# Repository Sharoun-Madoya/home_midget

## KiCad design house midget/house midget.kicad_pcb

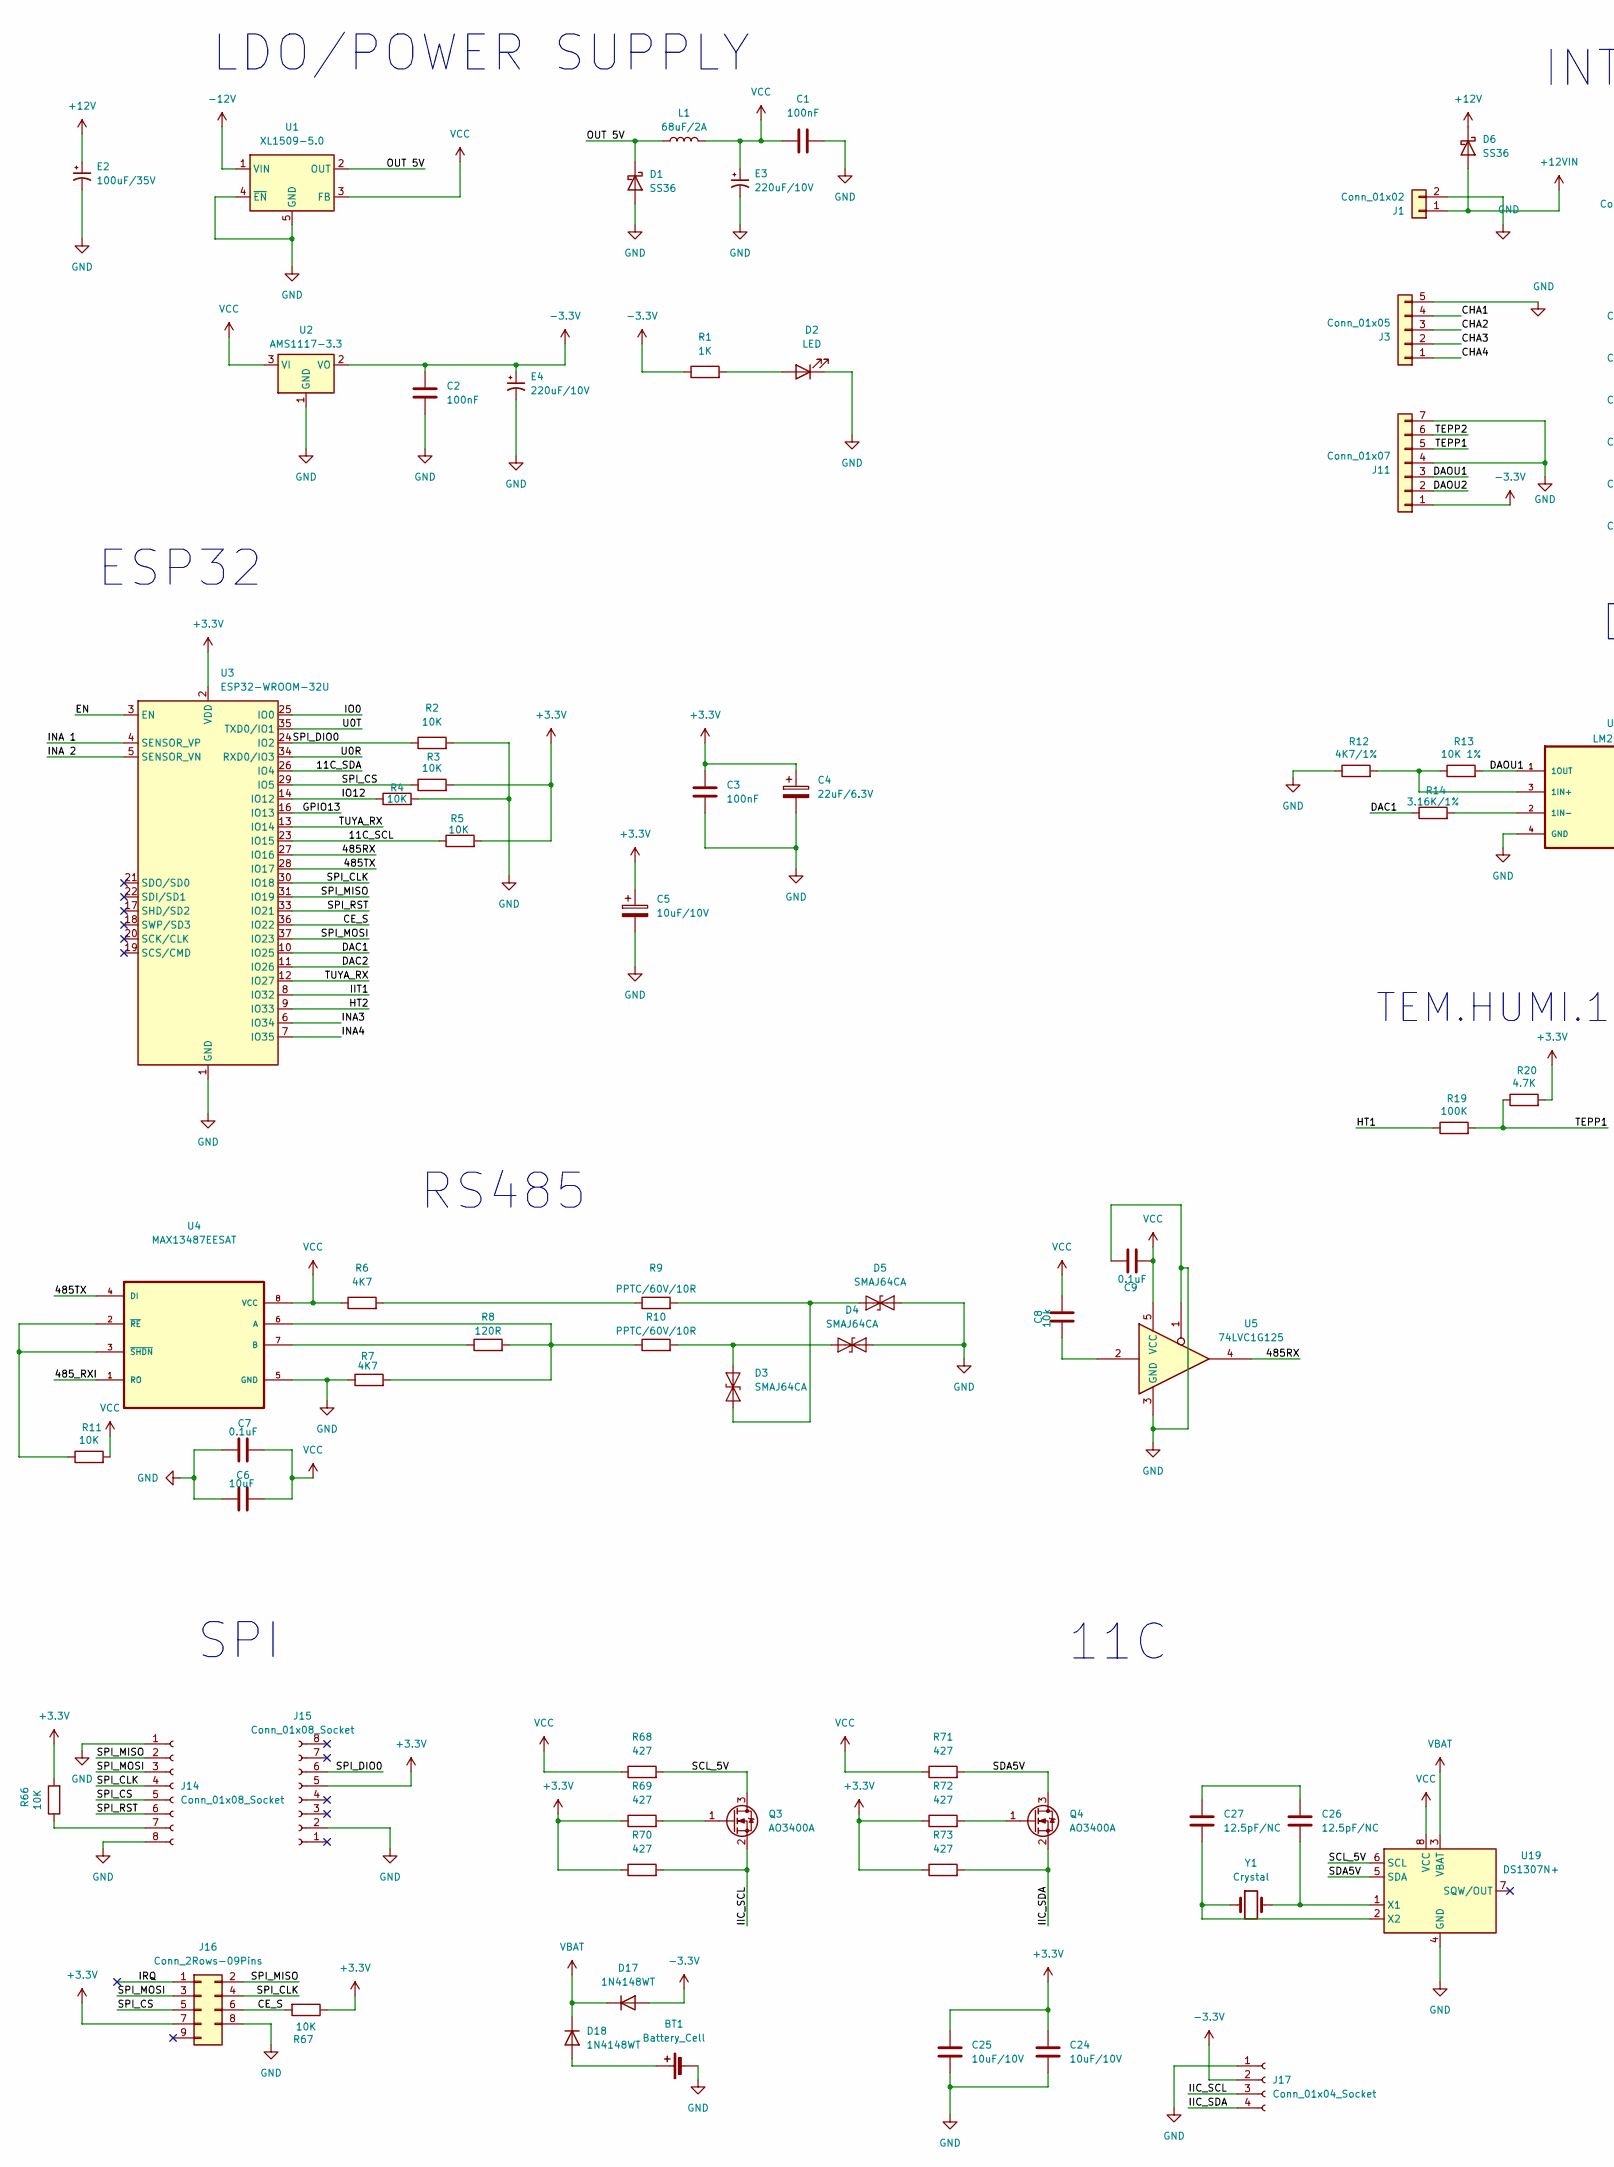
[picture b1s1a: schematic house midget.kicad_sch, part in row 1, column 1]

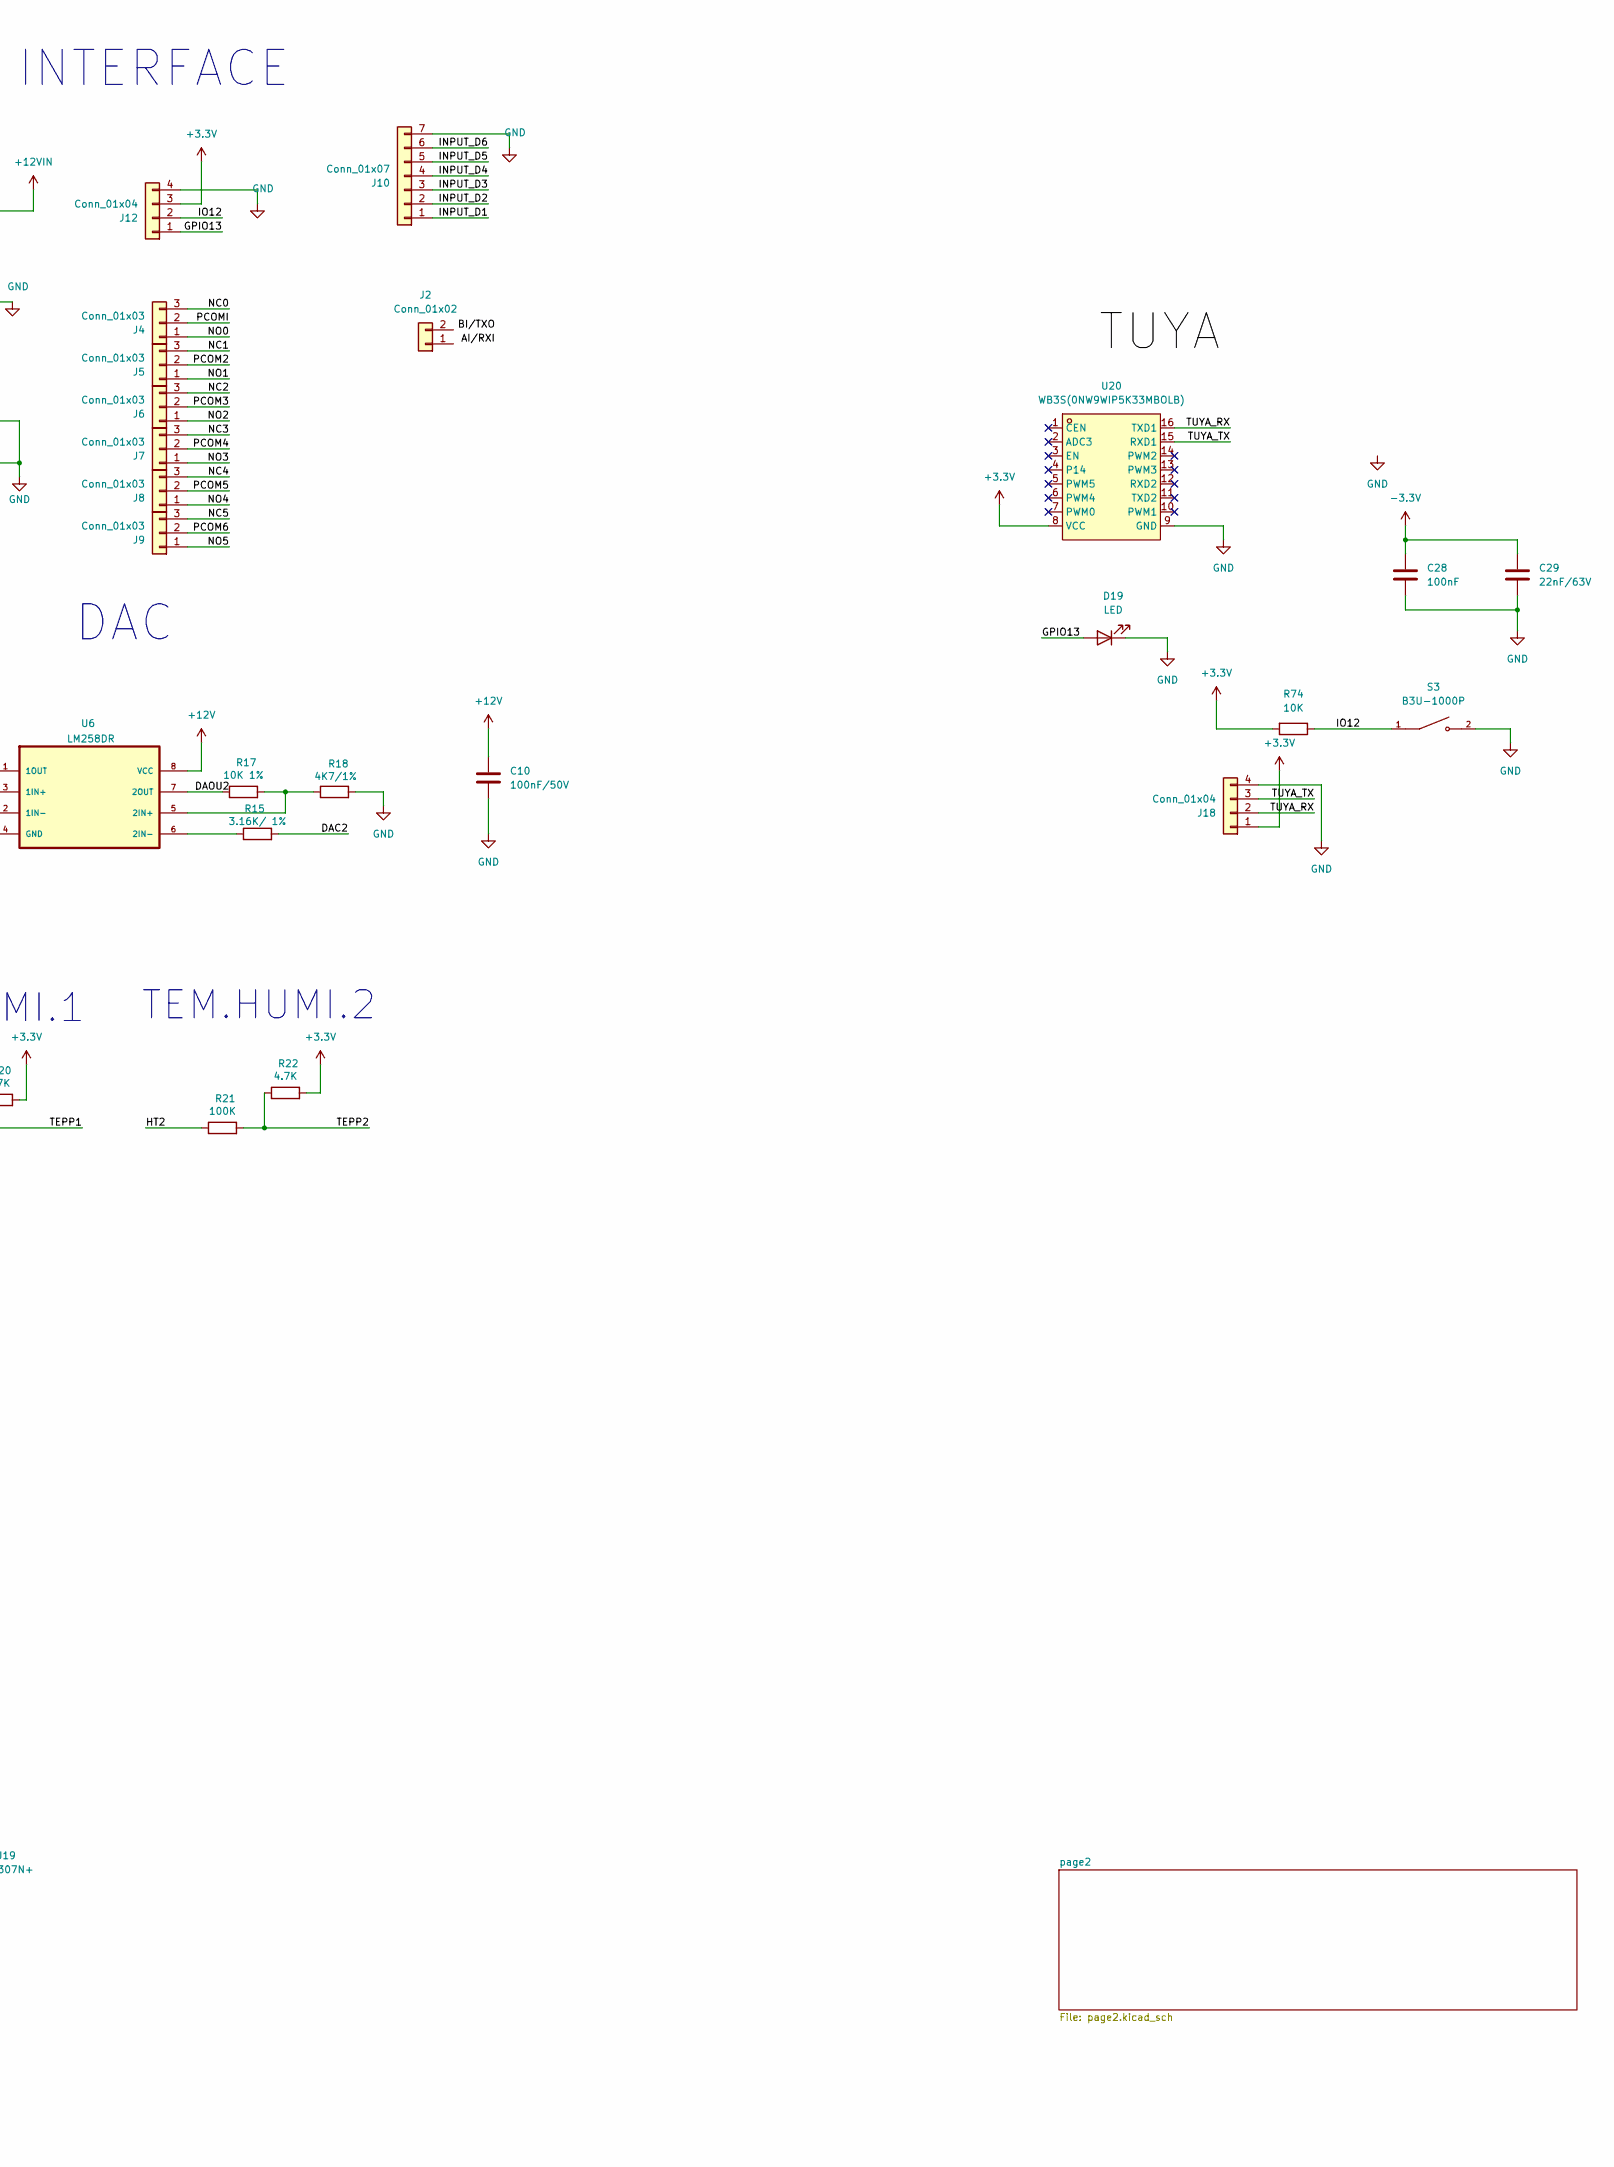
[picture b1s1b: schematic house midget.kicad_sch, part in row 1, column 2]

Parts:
BT1: Battery_Cell; BatteryHolder_MPD_BH-18650-PC2
C1, C2, C3, C28: 100nF; CP_EIA-3216-18_Kemet-A
C4: 22uF/6.3V; CP_EIA-3528-21_Kemet-B
C5, C24, C25: 10uF/10V; CP_EIA-2012-12_Kemet-R
C6: 10uF; CP_EIA-2012-12_Kemet-R
C7, C9: 0.1uF; C_1825_4564Metric
C8: 10k; CP_EIA-2012-12_Kemet-R
C10: 100nF/50V; CP_EIA-3216-18_Kemet-A
C26, C27: 12.5pF/NC; CP_EIA-2012-12_Kemet-R
C29: 22nF/63V; CP_EIA-3528-21_Kemet-B
D1: SS36; D_DO-35_SOD27_P7.62mm_Horizontal
D2, D19: LED; LED_Cree-XP
D3, D4, D5: SMAJ64CA; D_SMA
D6: SS36; D_SMA
D17, D18: 1N4148WT; D_SOD-523
E2: 100uF/35V; C_1808_4520Metric_Pad1.72x2.30mm_HandSolder
E3, E4: 220uF/10V; C_1808_4520Metric_Pad1.72x2.30mm_HandSolder
J1, J2: Conn_01x02; Flipper_Zero_Angled
J3: Conn_01x05; Flipper_Zero_Angled
J4, J5, J6, J7, J8, J9: Conn_01x03; Flipper_Zero_Angled
J10, J11: Conn_01x07; Flipper_Zero_Angled
J12, J18: Conn_01x04; Flipper_Zero_Angled
J14, J15: Conn_01x08_Socket; Flipper_Zero_Angled
J16: Conn_2Rows-09Pins; Flipper_Zero_Straight
J17: Conn_01x04_Socket; Flipper_Zero_Angled
L1: 68uF/2A; L_Sunlord_MWSA0605S
Q3, Q4: AO3400A; SOT-23
R1: 1K; R_1206_3216Metric
R2, R3, R4, R5, R11, R74: 10K; R_0805_2012Metric
R6, R7: 4K7; R_Axial_DIN0309_L9.0mm_D3.2mm_P15.24mm_Horizontal
R8: 120R; R_Axial_DIN0309_L9.0mm_D3.2mm_P15.24mm_Horizontal
R9, R10: PPTC/60V/10R; R_Axial_DIN0309_L9.0mm_D3.2mm_P15.24mm_Horizontal
R12, R18: 4K7/1%; R_Axial_DIN0309_L9.0mm_D3.2mm_P15.24mm_Horizontal
R13, R17: 10K 1%; R_0805_2012Metric
R14: 3.16K/1%; R_1206_3216Metric
R15: 3.16K/ 1%; R_1206_3216Metric
R19, R21: 100K; R_Axial_DIN0309_L9.0mm_D3.2mm_P15.24mm_Horizontal
R20, R22: 4.7K; R_Axial_DIN0309_L9.0mm_D3.2mm_P15.24mm_Horizontal
R66, R67: 10K; R_0201_0603Metric
R68, R69, R70, R71, R72, R73: 427; R_01005_0402Metric_Pad0.57x0.30mm_HandSolder
S3: B3U-1000P; SW_B3U-1000P; DigiKey_Part_Number SW1020TR-ND
U1: XL1509-5.0; SOIC-8_3.9x4.9mm_P1.27mm
U2: AMS1117-3.3; SOT-223-3_TabPin2
U3: ESP32-WROOM-32U
U4: MAX13487EESAT; SOIC127P600X175-8N
U5: 74LVC1G125; SOIC127P600X175-14N
U6: LM258DR; SOIC127P599X175-8N; DigiKey_Part_Number 296-14591-2-ND
U19: DS1307N+; DIP-8_W7.62mm
U20: WB3S(0NW9WIP5K33MBOLB); WB3S-SMD_OEAKA9ADCKYHKZYS; LCSC Part C2830108
Y1: Crystal; Oscillator_SMD_Fox_FT5H_5.0x3.2mm

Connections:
+3.3V: C3.2, C4.1, C5.1, C24.1, C25.1, J12.3, J15.5, J16.7, J18.1, R3.2, R5.2, R20.2, R22.2, R66.2, R67.1, R69.1, R70.1, R72.1, R73.1, R74.2, U3.2 (VDD), U20.8 (VCC); also elsewhere on the board
+12V: C10.2, D6.1 (K), E2.1, U6.8 (VCC)
+12VIN: D6.2 (A), J1.1; also elsewhere on the board
-3.3V: C2.2, C28.1, C29.1, D17.2 (A), E4.1, J11.1, J17.2, R1.1, U2.2 (VO); also elsewhere on the board
-12V: U1.1 (VIN)
/11C_SCL: R5.1, U3.23 (IO15)
/11C_SDA: U3.26 (IO4)
/485RX: U3.27 (IO16), U5.4
/485TX: U3.28 (IO17), U4.4 (DI)
/CE_S: J16.6, R67.2, U3.36 (IO22)
/CHA1: J3.4
/CHA2: J3.3
/CHA3: J3.2
/CHA4: J3.1
/DAC1: R14.1, U3.10 (IO25)
/DAC2: R15.2, U3.11 (IO26)
/DAOU1: J11.3, R13.2, U6.1 (1OUT)
/DAOU2: J11.2, R17.1, U6.7 (2OUT)
/EN: U3.3 (EN)
/GPIO13: D19.2 (A), J12.1, U3.16 (IO13)
/HT1: R19.1
/HT2: R21.1, U3.9 (IO33)
/IIC_SCL: J17.3, Q3.2 (S), R70.2
/IIC_SDA: J17.4, Q4.2 (S), R73.2
/IIT1: U3.8 (IO32)
/INA3: U3.6 (IO34)
/INA4: U3.7 (IO35)
/INA 1: U3.4 (SENSOR_VP)
/INA 2: U3.5 (SENSOR_VN)
/INPUT_D1: J10.1
/INPUT_D2: J10.2
/INPUT_D3: J10.3
/INPUT_D4: J10.4
/INPUT_D5: J10.5
/INPUT_D6: J10.6
/IO0: U3.25 (IO0)
/IO12: J12.2, R4.1, R74.1, S3.1, U3.14 (IO12)
/IRQ: J16.1
/NC0: J4.3
/NC1: J5.3
/NC2: J6.3
/NC3: J7.3
/NC4: J8.3
/NC5: J9.3
/NO0: J4.1
/NO1: J5.1
/NO2: J6.1
/NO3: J7.1
/NO4: J8.1
/NO5: J9.1
/OUT 5V: D1.1 (K), L1.1, U1.2 (OUT)
/PCOM2: J5.2
/PCOM3: J6.2
/PCOM4: J7.2
/PCOM5: J8.2
/PCOM6: J9.2
/PCOMI: J4.2
/SCL_5V: Q3.3 (D), R68.2, U19.6 (SCL)
/SDA5V: Q4.3 (D), R71.2, U19.5 (SDA)
/SPI_CLK: J14.4, J16.4, U3.30 (IO18)
/SPI_CS: J14.5, J16.5, R3.1, U3.29 (IO5)
/SPI_DIO0: J15.6, R2.1, U3.24 (IO2)
/SPI_MISO: J14.2, J16.2, U3.31 (IO19)
/SPI_MOSI: J14.3, J16.3, U3.37 (IO23)
/SPI_RST: J14.6, U3.33 (IO21)
/TEPP1: J11.5, R19.2, R20.1
/TEPP2: J11.6, R21.2, R22.1
/TUYA_RX: J18.2, U3.12 (IO27), U3.13 (IO14), U20.16 (TXD1)
/TUYA_TX: J18.3, U20.15 (RXD1)
/U0R: U3.34 (RXD0/IO3)
/U0T: U3.35 (TXD0/IO1)
GND: BT1.2 (-), C1.2, C2.1, C3.1, C4.2, C5.2, C6.2, C7.2, C9.1, C10.1, C24.2, C25.2, C28.2, C29.2, D1.2 (A), D2.1 (K), D4.1 (A1), D5.1 (A1), D19.1 (K), E2.2, E3.2, E4.2, J1.2, J3.5, J10.7, J11.4, J11.7, J12.4, J14.1, J14.8, J15.2, J16.8, J17.1, J18.4, R2.2, R4.2, R7.1, R12.1, R18.2, S3.2, U1.4 (~EN), U1.5 (GND), U1.6 (GND), U1.7 (GND), U1.8 (GND), U2.1 (GND), U3.1 (GND), U3.15 (GND), U3.38 (GND), U3.39 (GND), U4.5 (GND), U5.1, U5.3 (GND), U6.4 (GND), U19.4 (GND), U20.9 (GND); also elsewhere on the board
unnamed: BT1.1 (+), D18.2 (A)
unnamed: C8.2, U5.2
unnamed: C26.1, C27.1
unnamed: D2.2 (A), R1.2
unnamed: D3.1 (A1), D5.2 (A2), R9.2
unnamed: D3.2 (A2), D4.2 (A2), R10.2
unnamed: J14.7, R66.1
unnamed: Q3.1 (G), R69.2
unnamed: Q4.1 (G), R72.2
unnamed: R6.2, R9.1
unnamed: R7.2, R8.2, R10.1, U4.6 (A)
unnamed: R8.1, U4.7 (B)
unnamed: R11.1, U4.2 (~RE), U4.3 (~SHDN)
unnamed: R12.2, R13.1, U6.3 (1IN+)
unnamed: R14.2, U6.2 (1IN-)
unnamed: R17.2, R18.1, U6.5 (2IN+)
unnamed: R15.1, U6.6 (2IN-)
unnamed: C26.2, U19.1 (X1), Y1.2
unnamed: C27.2, U19.2 (X2), Y1.1
VBAT: D17.1 (K), D18.1 (K), U19.3 (VBAT)
VCC: C1.1, C6.1, C7.1, C8.1, C9.2, E3.1, L1.2, R6.1, R11.2, R68.1, R71.1, U1.3 (FB), U2.3 (VI), U4.8 (VCC), U5.5 (VCC), U19.8 (VCC); also elsewhere on the board

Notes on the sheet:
ESP32
11C
DAC
RS485
TEM.HUMI.2
INTERFACE
TEM.HUMI.1
SPI
LDO/POWER SUPPLY

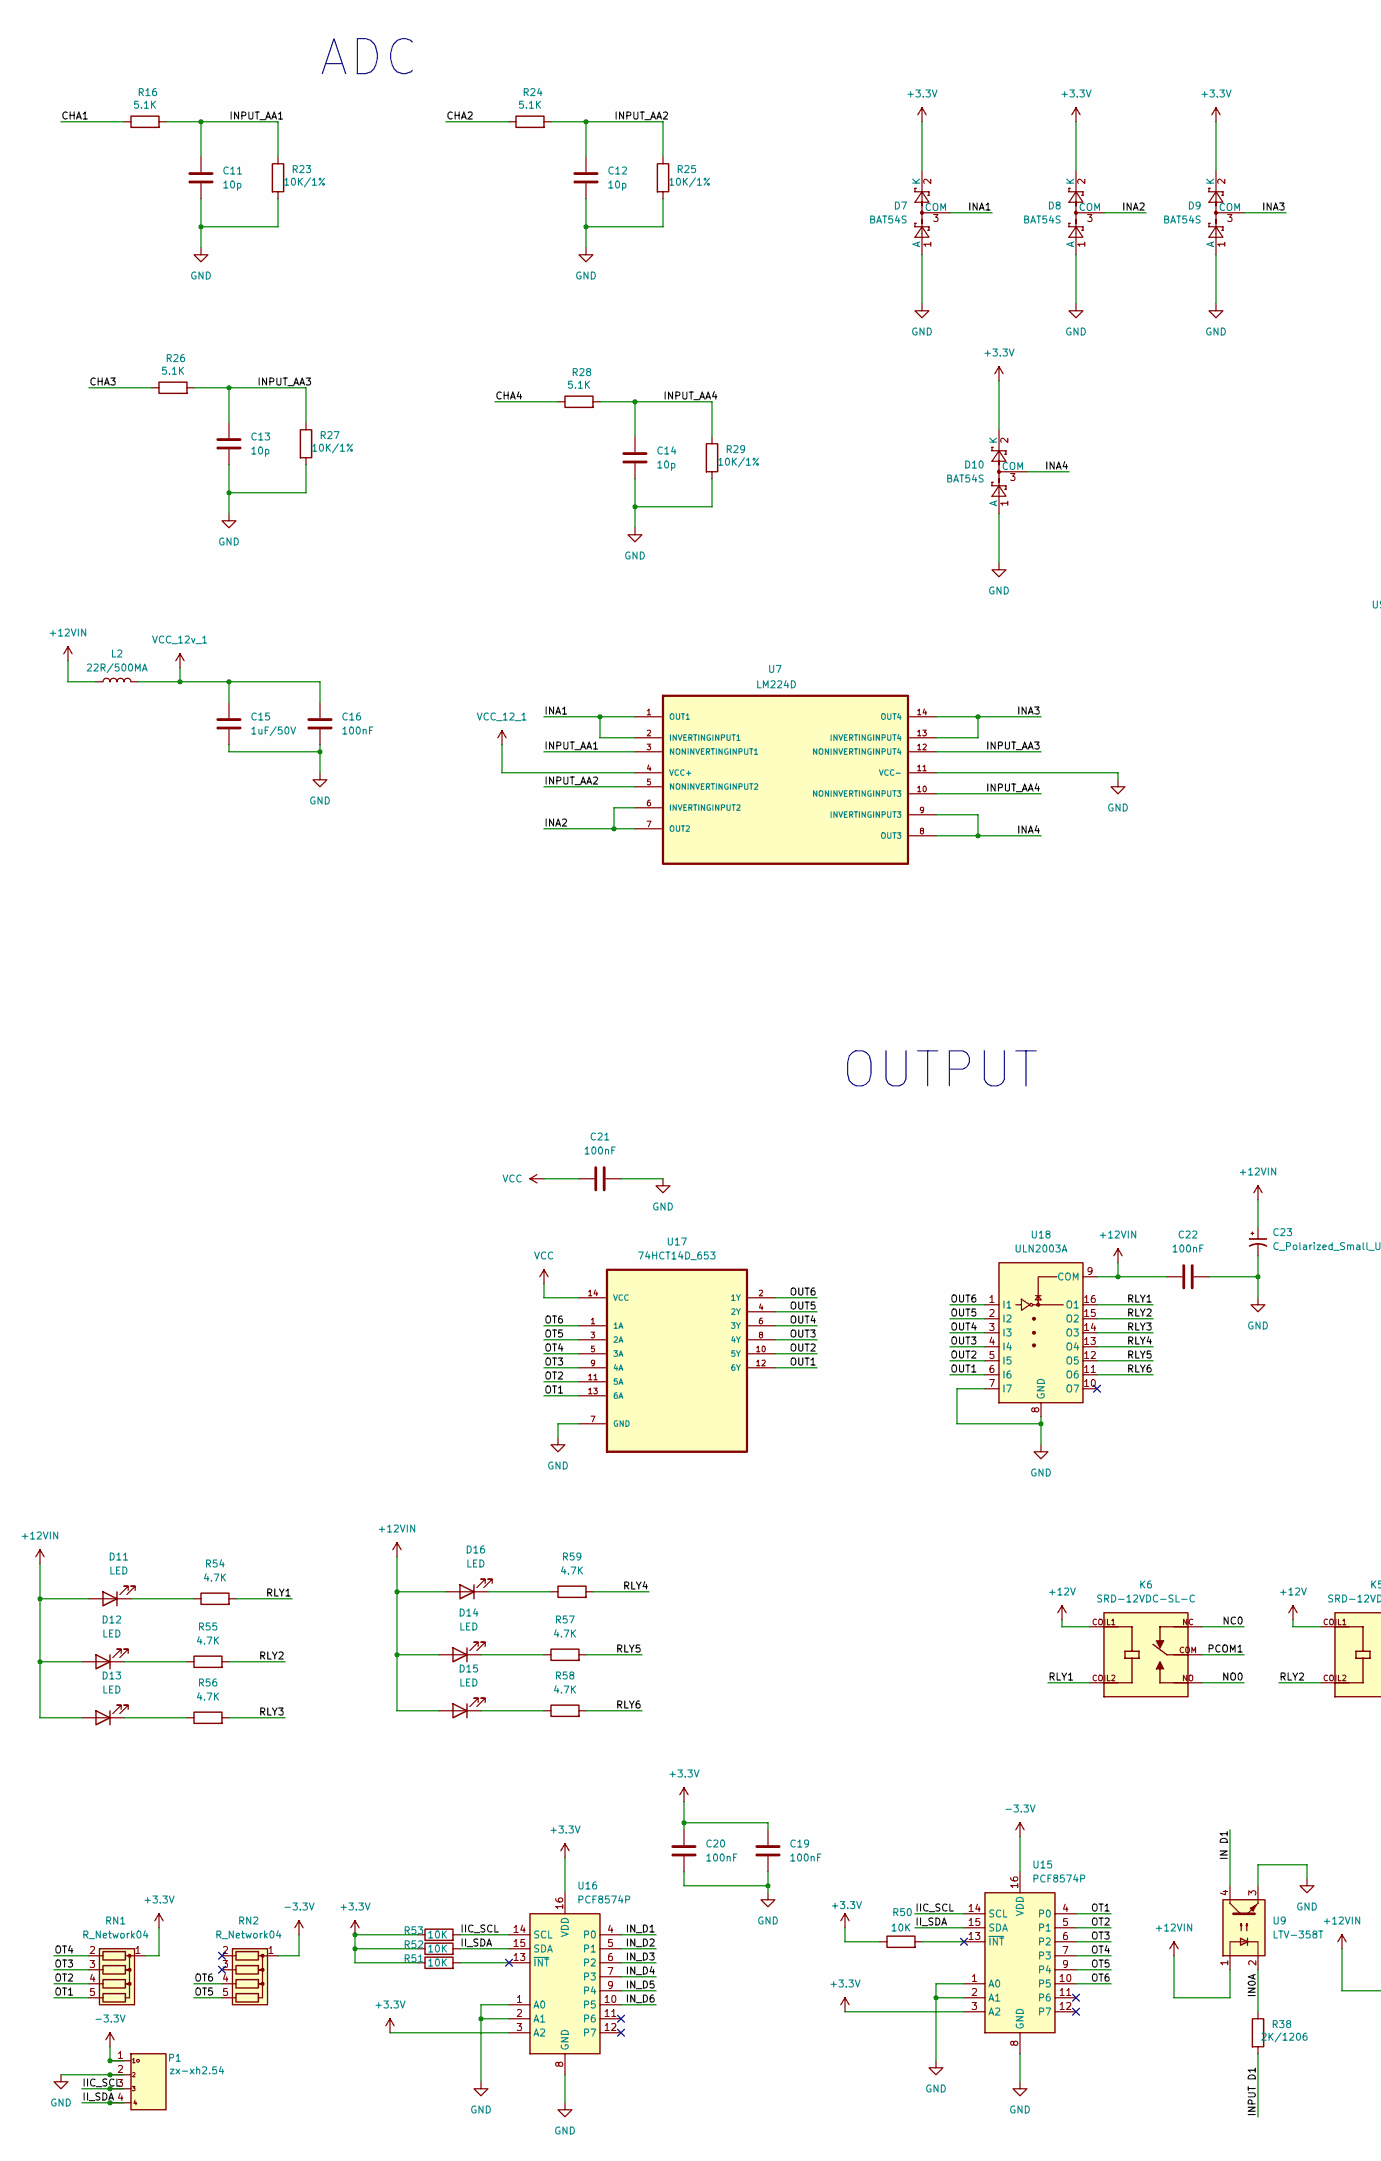
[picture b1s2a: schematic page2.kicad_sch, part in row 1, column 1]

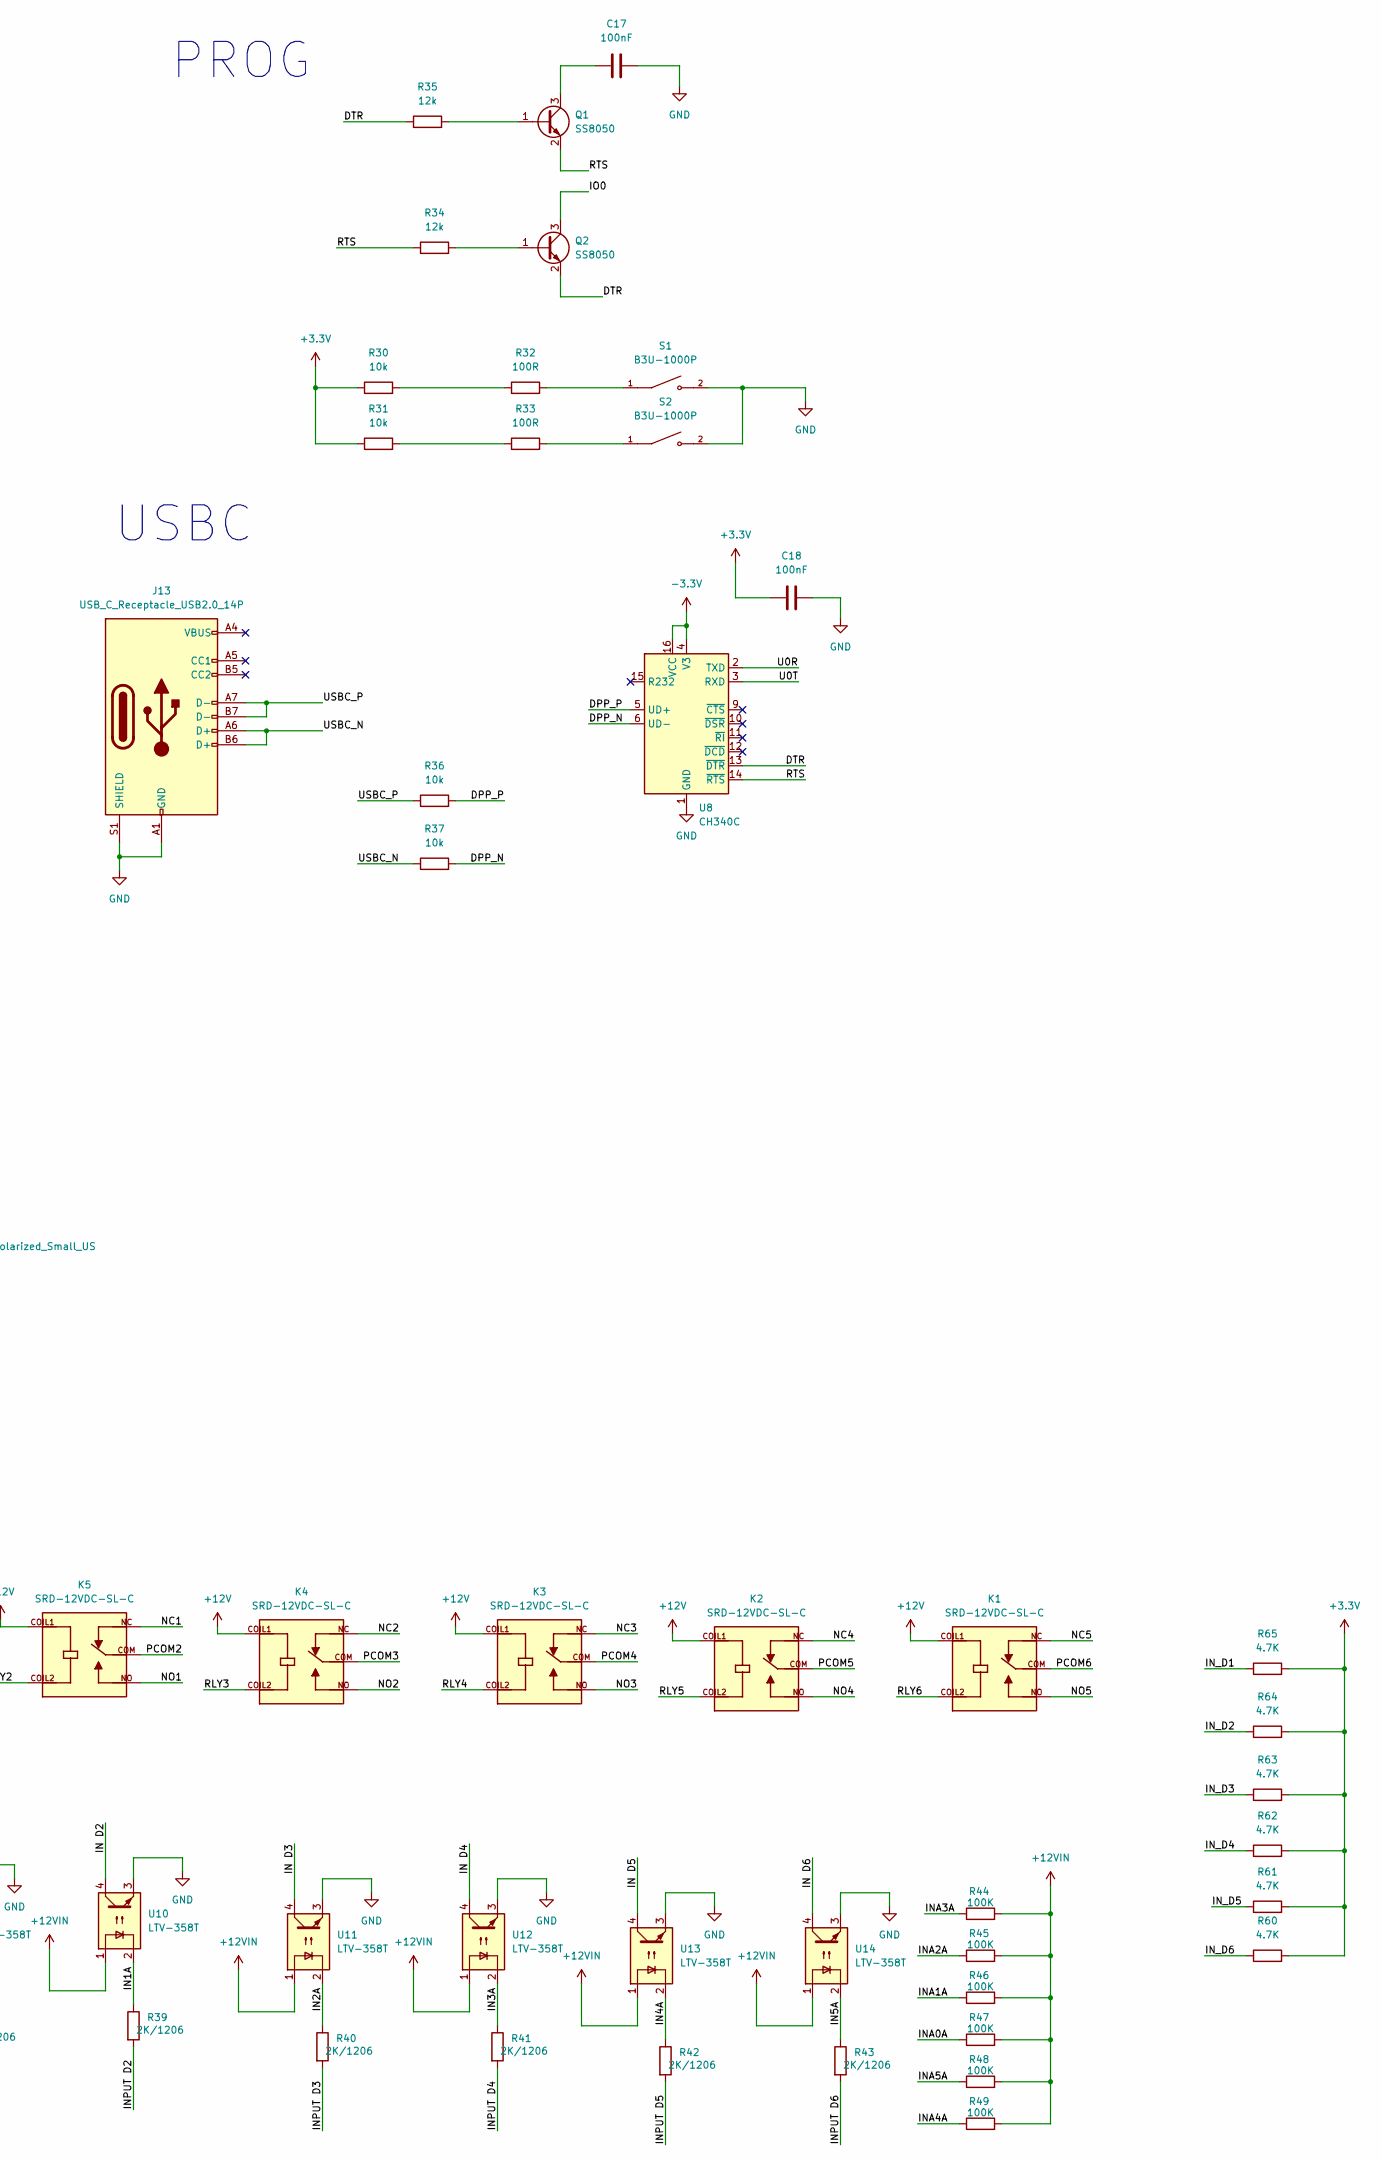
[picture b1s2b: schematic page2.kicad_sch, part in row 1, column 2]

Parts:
C11, C12, C13, C14: 10p; CP_EIA-2012-12_Kemet-R
C15: 1uF/50V; C_1825_4564Metric
C16, C17, C18, C19, C20, C21, C22: 100nF; CP_EIA-3216-18_Kemet-A
C23: C_Polarized_Small_US; C_1825_4564Metric
D7, D8, D9, D10: BAT54S; SOT-23
D11, D12, D13, D14, D15, D16: LED; LED_Cree-XP
J13: USB_C_Receptacle_USB2.0_14P; USB_C_Receptacle_GCT_USB4105-xx-A_16P_TopMnt_Horizontal
K1, K2, K3, K4, K5, K6: SRD-12VDC-SL-C; RELAY_SRD-12VDC-SL-C; PARTREV 1.0
L2: 22R/500MA; L_Sunlord_MWSA0605S
P1: zx-xh2.54; L_Sunlord_MWSA0605S
Q1, Q2: SS8050; SOT-23
R16, R24, R26, R28: 5.1K; R_Axial_DIN0309_L9.0mm_D3.2mm_P15.24mm_Horizontal
R23, R25, R27, R29: 10K/1%; R_0805_2012Metric
R30, R31, R36, R37: 10k; R_0805_2012Metric
R32, R33: 100R; R_1218_3246Metric
R34, R35: 12k; R_0805_2012Metric
R38, R39, R40, R41, R42, R43: 2K/1206; R_1206_3216Metric
R44, R45, R46, R47, R48, R49: 100K; R_1218_3246Metric
R50, R51, R52, R53: 10K; R_Axial_DIN0614_L14.3mm_D5.7mm_P5.08mm_Vertical
R54, R55, R56, R57, R58, R59, R60, R61, R62, R63, R64, R65: 4.7K; R_1206_3216Metric
RN1, RN2: R_Network04; R_Array_SIP5
S1, S2: B3U-1000P; SW_B3U-1000P; DigiKey_Part_Number SW1020TR-ND
U7: LM224D; SOIC127P600X175-14N
U8: CH340C; SOIC-16_3.9x9.9mm_P1.27mm
U9, U10, U11, U12, U13, U14: LTV-358T; SO-4_4.4x3.6mm_P2.54mm
U15, U16: PCF8574P; DIP-16_W7.62mm
U17: 74HCT14D_653; SOIC127P600X175-14N; MPN 74HCT14D,653; DigiKey_Part_Number 1727-2836-2-ND
U18: ULN2003A; SOIC127P600X175-16N

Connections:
+3.3V: C18.1, C19.1, C20.1, D7.2 (K), D8.2 (K), D9.2 (K), D10.2 (K), R30.1, R31.1, R50.1, R51.1, R52.1, R53.1, R60.2, R61.2, R62.2, R63.2, R64.2, R65.2, RN1.1 (common), U15.3 (A2), U16.3 (A2), U16.16 (VDD); also elsewhere on the board
+12VIN: C22.1, C23.1, D11.2 (A), D12.2 (A), D13.2 (A), D14.2 (A), D15.2 (A), D16.2 (A), L2.1, R44.2, R45.2, R46.2, R47.2, R48.2, R49.2, U9.1, U10.1, U11.1, U12.1, U13.1, U14.1, U18.9 (COM); also elsewhere on the board
-3.3V: P1.1, RN2.1 (common), U8.4 (V3), U8.16 (VCC), U15.16 (VDD); also elsewhere on the board
/page2/CHA1: R16.1
/page2/CHA2: R24.1
/page2/CHA3: R26.1
/page2/CHA4: R28.1
/page2/DPP_N: R37.2, U8.6 (UD-)
/page2/DPP_P: R36.2, U8.5 (UD+)
/page2/DTR: Q2.2 (E), R35.1, U8.13 (~DTR)
/page2/IIC_SCL: P1.3, R53.2, U15.14 (SCL), U16.14 (SCL)
/page2/II_SDA: P1.4, R52.2, U15.15 (SDA), U16.15 (SDA)
/page2/IN0A: R38.1, U9.2
/page2/IN1A: R39.1, U10.2
/page2/IN2A: R40.1, U11.2
/page2/IN3A: R41.1, U12.2
/page2/IN4A: R42.1, U13.2
/page2/IN5A: R43.1, U14.2
/page2/IN D1: U9.4
/page2/IN D2: U10.4
/page2/IN D3: U11.4
/page2/IN D4: U12.4
/page2/IN D5: U13.4
/page2/IN D6: U14.4
/page2/INA0A: R47.1
/page2/INA1: D7.3 (COM), U7.1 (OUT1), U7.2 (INVERTINGINPUT1)
/page2/INA1A: R46.1
/page2/INA2: D8.3 (COM), U7.6 (INVERTINGINPUT2), U7.7 (OUT2)
/page2/INA2A: R45.1
/page2/INA3: D9.3 (COM), U7.13 (INVERTINGINPUT4), U7.14 (OUT4)
/page2/INA3A: R44.1
/page2/INA4: D10.3 (COM), U7.8 (OUT3), U7.9 (INVERTINGINPUT3)
/page2/INA4A: R49.1
/page2/INA5A: R48.1
/page2/INPUT D1: R38.2
/page2/INPUT D2: R39.2
/page2/INPUT D3: R40.2
/page2/INPUT D4: R41.2
/page2/INPUT D5: R42.2
/page2/INPUT D6: R43.2
/page2/INPUT_AA1: C11.1, R16.2, R23.1, U7.3 (NONINVERTINGINPUT1)
/page2/INPUT_AA2: C12.1, R24.2, R25.1, U7.5 (NONINVERTINGINPUT2)
/page2/INPUT_AA3: C13.1, R26.2, R27.1, U7.12 (NONINVERTINGINPUT4)
/page2/INPUT_AA4: C14.1, R28.2, R29.1, U7.10 (NONINVERTINGINPUT3)
/page2/IN_D1: R65.1, U16.4 (P0)
/page2/IN_D2: R64.1, U16.5 (P1)
/page2/IN_D3: R63.1, U16.6 (P2)
/page2/IN_D4: R62.1, U16.7 (P3)
/page2/IN_D5: R61.1, U16.9 (P4)
/page2/IN_D6: R60.1, U16.10 (P5)
/page2/IO0: Q2.3 (C)
/page2/OT1: RN1.5 (R4), U15.4 (P0), U17.13 (6A)
/page2/OT2: RN1.4 (R3), U15.5 (P1), U17.11 (5A)
/page2/OT3: RN1.3 (R2), U15.6 (P2), U17.9 (4A)
/page2/OT4: RN1.2 (R1), U15.7 (P3), U17.5 (3A)
/page2/OT5: RN2.5 (R4), U15.9 (P4), U17.3 (2A)
/page2/OT6: RN2.4 (R3), U15.10 (P5), U17.1 (1A)
/page2/RLY1: K6.COIL2, R54.2, U18.16 (O1)
/page2/RLY2: K5.COIL2, R55.2, U18.15 (O2)
/page2/RLY3: K4.COIL2, R56.2, U18.14 (O3)
/page2/RLY4: K3.COIL2, R59.2, U18.13 (O4)
/page2/RLY5: K2.COIL2, R57.2, U18.12 (O5)
/page2/RLY6: K1.COIL2, R58.2, U18.11 (O6)
/page2/RTS: Q1.2 (E), R34.1, U8.14 (~RTS)
/page2/U0R: U8.2 (TXD)
/page2/U0T: U8.3 (RXD)
/page2/USBC_N: J13.A6 (D+), J13.B6 (D+), R37.1
/page2/USBC_P: J13.A7 (D-), J13.B7 (D-), R36.1
GND: C11.2, C12.2, C13.2, C14.2, C15.2, C16.2, C17.2, C18.2, C19.2, C20.2, C21.2, C22.2, C23.2, D7.1 (A), D8.1 (A), D9.1 (A), D10.1 (A), J13.A1 (GND), J13.A12 (GND), J13.B1 (GND), J13.B12 (GND), J13.S1 (SHIELD), P1.2, R23.2, R25.2, R27.2, R29.2, S1.2, S2.2, U7.11 (VCC-), U8.1 (GND), U9.3, U10.3, U11.3, U12.3, U13.3, U14.3, U15.1 (A0), U15.2 (A1), U15.8 (GND), U16.1 (A0), U16.2 (A1), U16.8 (GND), U17.7 (GND), U18.7 (I7), U18.8 (GND); also elsewhere on the board
unnamed: D11.1 (K), R54.1
unnamed: D12.1 (K), R55.1
unnamed: D13.1 (K), R56.1
unnamed: D14.1 (K), R57.1
unnamed: D15.1 (K), R58.1
unnamed: D16.1 (K), R59.1
unnamed: K1.COIL1, K2.COIL1, K3.COIL1, K4.COIL1, K5.COIL1, K6.COIL1
unnamed: Q1.1 (B), R35.2
unnamed: C17.1, Q1.3 (C)
unnamed: Q2.1 (B), R34.2
unnamed: R30.2, R32.1
unnamed: R31.2, R33.1
unnamed: R32.2, S1.1
unnamed: R33.2, S2.1
unnamed: U17.2 (1Y), U18.1 (I1)
unnamed: U17.4 (2Y), U18.2 (I2)
unnamed: U17.6 (3Y), U18.3 (I3)
unnamed: U17.8 (4Y), U18.4 (I4)
unnamed: U17.10 (5Y), U18.5 (I5)
unnamed: U17.12 (6Y), U18.6 (I6)
VCC: C21.1, U17.14 (VCC); also elsewhere on the board
VCC_12v_1: C15.1, C16.1, L2.2

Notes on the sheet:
ADC
OUTPUT
PROG
USBC

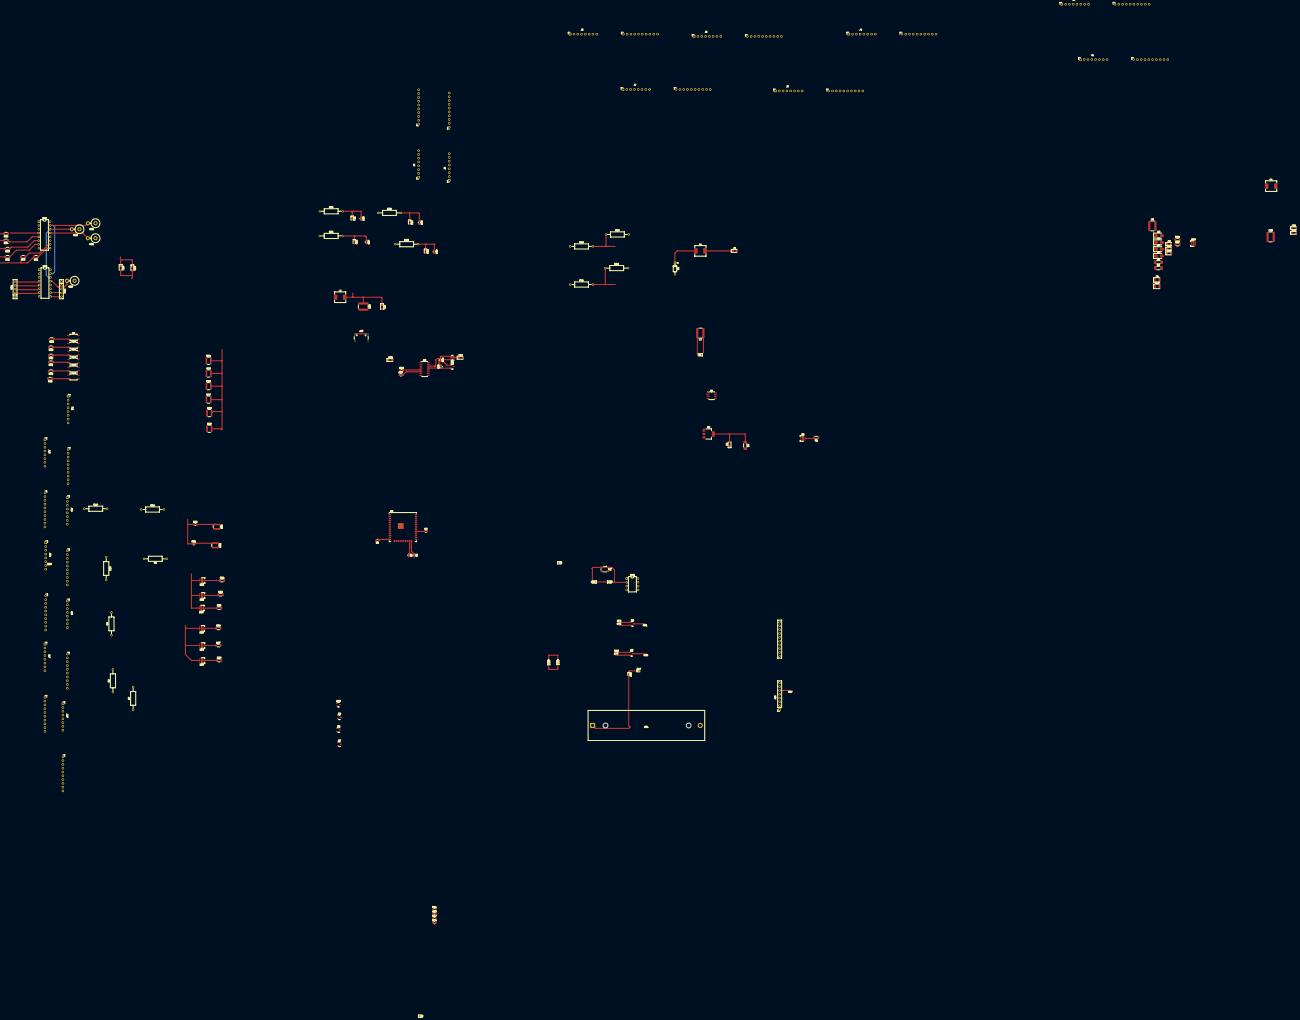
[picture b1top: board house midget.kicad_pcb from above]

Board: 2 copper layers, 167 parts (0 on the bottom side), 86 nets.

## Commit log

2025-04-19 :sparkles:done with rs45, esp32, dac, ldo
2025-04-20 :building_construction: USBC, PROG. PAGE 2
2025-04-21 :egg: output done
2025-04-21 :alembic:completed output
2025-04-23 :egg: completed schematics
2025-04-25 :tada: added tuya as last scematic part
2025-04-30 :tada: fintuning the footprint
2025-04-30 :memo: started 3d
2025-05-02 :bento: started with assembling simple components in editor
2025-05-14 :[200~:wrench: completed spi and 11c:
2025-05-15 :beers:pge 1 Done
2025-05-15 :beers: DONE WITH PROG AND ADC
2025-05-16 :construction: output added to editor
2025-05-21 :egg: started connecting ic
